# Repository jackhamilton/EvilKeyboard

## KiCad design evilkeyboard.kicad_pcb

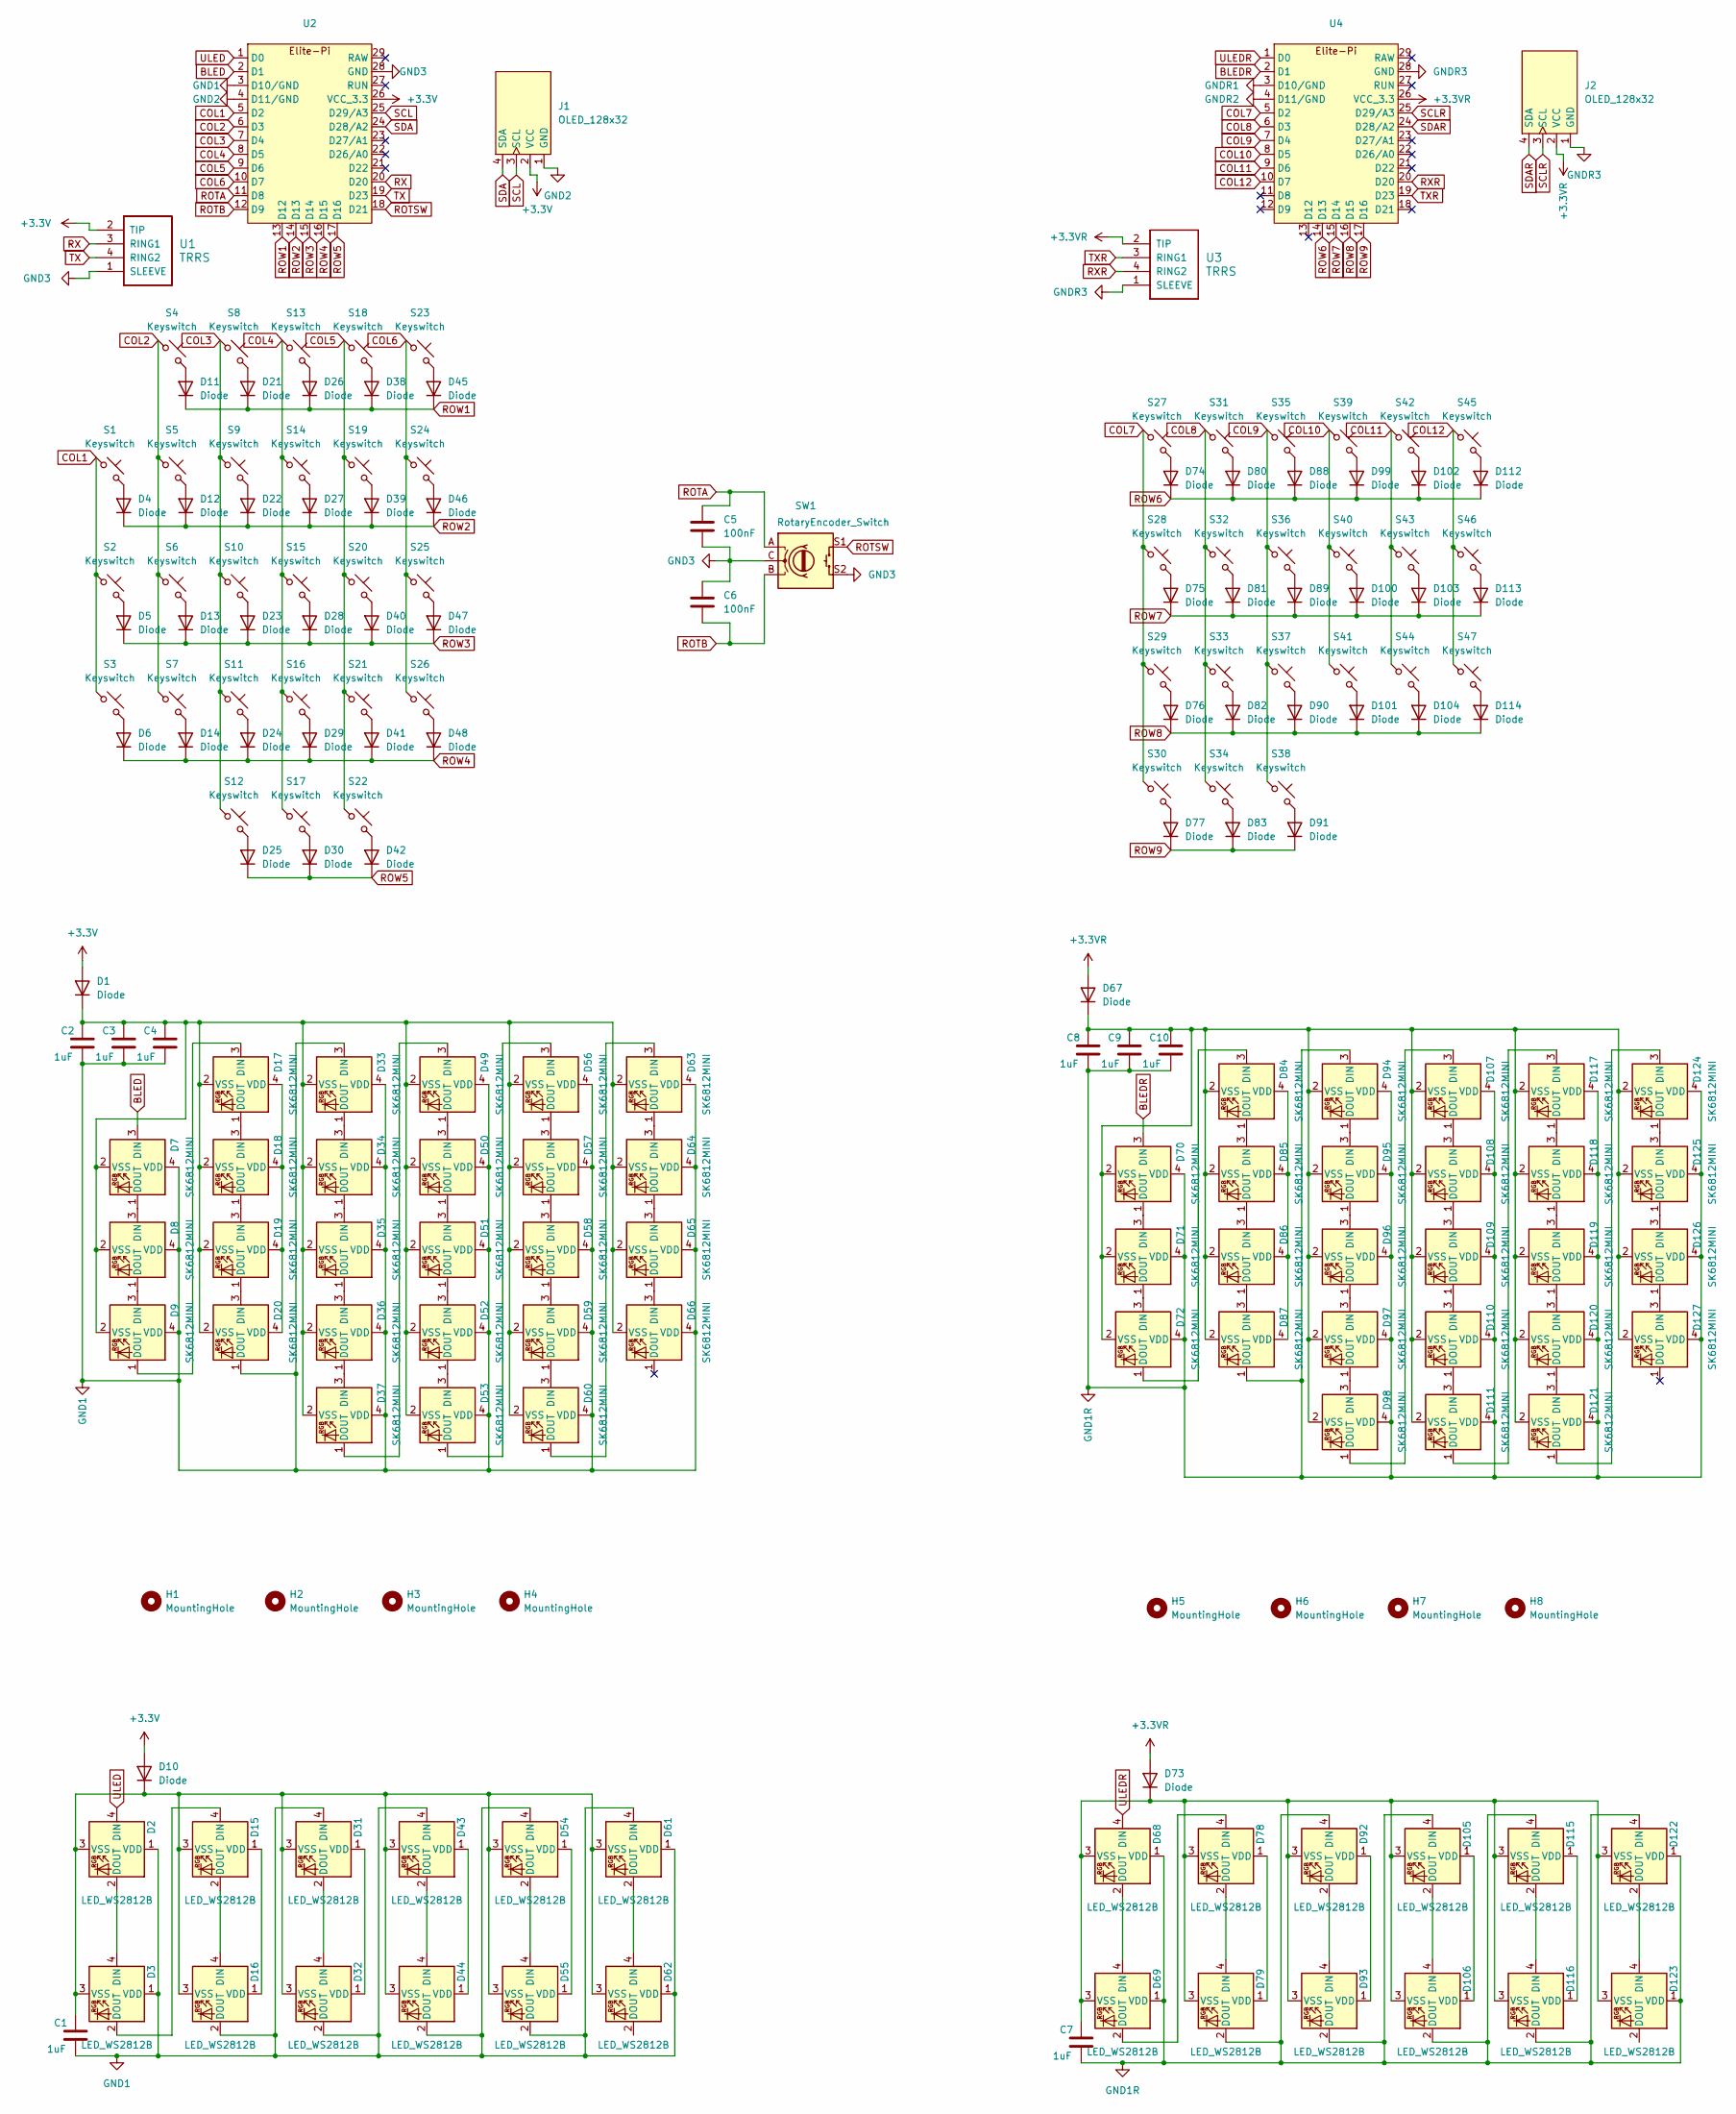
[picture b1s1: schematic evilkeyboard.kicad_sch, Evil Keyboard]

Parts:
C1, C2, C3, C4, C7, C8, C9, C10: 1uF; C_0201_0603Metric_Pad0.64x0.40mm_HandSolder
C5, C6: 100nF; C_0201_0603Metric_Pad0.64x0.40mm_HandSolder
D1, D4, D5, D6, D10, D11, D12, D13, D14, D21, D22, D23, D24, D25, D26, D27, D28, D29, D30, D38, D39, D40, D41, D42, D45, D46, D47, D48, D67, D73, D74, D75, D76, D77, D80, D81, D82, D83, D88, D89, D90, D91, D99, D100, D101, D102, D103, D104, D112, D113, D114: Diode
D2, D3, D15, D16, D31, D32, D43, D44, D54, D55, D61, D62, D68, D69, D78, D79, D92, D93, D105, D106, D115, D116, D122, D123: LED_WS2812B
D7, D8, D9, D17, D18, D19, D20, D33, D34, D35, D36, D37, D49, D50, D51, D52, D53, D56, D57, D58, D59, D60, D63, D64, D65, D66, D70, D71, D72, D84, D85, D86, D87, D94, D95, D96, D97, D98, D107, D108, D109, D110, D111, D117, D118, D119, D120, D121, D124, D125, D126, D127: SK6812MINI; LED_SK6812MINI_PLCC4_3.5x3.5mm_P1.75mm
H1, H2, H3, H4, H5, H6, H7, H8: MountingHole; MountingHole_2.7mm
J1, J2: OLED_128x32
S1, S2, S3, S4, S5, S6, S7, S8, S9, S10, S11, S12, S13, S14, S15, S16, S17, S18, S19, S20, S21, S22, S23, S24, S25, S26, S27, S28, S29, S30, S31, S32, S33, S34, S35, S36, S37, S38, S39, S40, S41, S42, S43, S44, S45, S46, S47: Keyswitch; Kailh_socket_PG1350
SW1: RotaryEncoder_Switch; RotaryEncoder_EC11
U1, U3: TRRS; TRRS_PJ-320A
U2, U4: Elite-C

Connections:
TX: U1.4 (RING2), U2.19 (D23)
TXR: U3.3 (RING1), U4.19 (D23)
+3.3V: D1.2 (A), D10.2 (A), J1.2 (VCC), U1.2 (TIP), U2.26 (VCC_3.3)
+3.3VR: D67.2 (A), D73.2 (A), J2.2 (VCC), U3.2 (TIP), U4.26 (VCC_3.3)
BLED: D7.3 (DIN), U2.2 (D1)
BLEDR: D70.3 (DIN), U4.2 (D1)
COL1: S1.1, S2.1, S3.1, U2.5 (D2)
COL2: S4.1, S5.1, S6.1, S7.1, U2.6 (D3)
COL3: S8.1, S9.1, S10.1, S11.1, S12.1, U2.7 (D4)
COL4: S13.1, S14.1, S15.1, S16.1, S17.1, U2.8 (D5)
COL5: S18.1, S19.1, S20.1, S21.1, S22.1, U2.9 (D6)
COL6: S23.1, S24.1, S25.1, S26.1, U2.10 (D7)
COL7: S27.1, S28.1, S29.1, S30.1, U4.5 (D2)
COL8: S31.1, S32.1, S33.1, S34.1, U4.6 (D3)
COL9: S35.1, S36.1, S37.1, S38.1, U4.7 (D4)
COL10: S39.1, S40.1, S41.1, U4.8 (D5)
COL11: S42.1, S43.1, S44.1, U4.9 (D6)
COL12: S45.1, S46.1, S47.1, U4.10 (D7)
GND1: C1.2, C2.2, C3.2, C4.2, D2.1 (VDD), D3.1 (VDD), D7.4 (VDD), D8.4 (VDD), D9.4 (VDD), D16.2 (DOUT), D20.1 (DOUT), D31.4 (DIN), D32.2 (DOUT), D33.3 (DIN), D33.4 (VDD), D34.4 (VDD), D35.4 (VDD), D36.4 (VDD), D37.4 (VDD), D43.4 (DIN), D44.2 (DOUT), D49.4 (VDD), D50.4 (VDD), D51.4 (VDD), D52.4 (VDD), D53.4 (VDD), D54.4 (DIN), D55.2 (DOUT), D56.4 (VDD), D57.4 (VDD), D58.4 (VDD), D59.4 (VDD), D60.4 (VDD), D61.1 (VDD), D61.4 (DIN), D62.1 (VDD), D63.4 (VDD), D64.4 (VDD), D65.4 (VDD), D66.4 (VDD), U2.3 (D10/GND)
GND1R: C7.2, C8.2, C9.2, C10.2, D68.1 (VDD), D69.1 (VDD), D70.4 (VDD), D71.4 (VDD), D72.4 (VDD), D79.2 (DOUT), D87.1 (DOUT), D92.4 (DIN), D93.2 (DOUT), D94.3 (DIN), D94.4 (VDD), D95.4 (VDD), D96.4 (VDD), D97.4 (VDD), D98.4 (VDD), D105.4 (DIN), D106.2 (DOUT), D107.4 (VDD), D108.4 (VDD), D109.4 (VDD), D110.4 (VDD), D111.4 (VDD), D115.4 (DIN), D116.2 (DOUT), D117.4 (VDD), D118.4 (VDD), D119.4 (VDD), D120.4 (VDD), D121.4 (VDD), D122.1 (VDD), D122.4 (DIN), D123.1 (VDD), D124.4 (VDD), D125.4 (VDD), D126.4 (VDD), D127.4 (VDD)
GND2: J1.1 (GND), U2.4 (D11/GND)
GND3: C5.2, C6.1, SW1.C, SW1.S2, U1.1 (SLEEVE), U2.28 (GND)
GNDR1: U4.3 (D10/GND)
GNDR2: U4.4 (D11/GND)
GNDR3: J2.1 (GND), U3.1 (SLEEVE), U4.28 (GND)
unnamed: C2.1, C3.1, C4.1, D1.1 (K), D7.2 (VSS), D8.2 (VSS), D9.2 (VSS), D17.2 (VSS), D18.2 (VSS), D19.2 (VSS), D20.2 (VSS), D33.2 (VSS), D34.2 (VSS), D35.2 (VSS), D36.2 (VSS), D37.2 (VSS), D49.2 (VSS), D50.2 (VSS), D51.2 (VSS), D52.2 (VSS), D53.2 (VSS), D56.2 (VSS), D57.2 (VSS), D58.2 (VSS), D59.2 (VSS), D60.2 (VSS), D63.2 (VSS), D64.2 (VSS), D65.2 (VSS), D66.2 (VSS)
unnamed: D2.2 (DOUT), D3.4 (DIN)
unnamed: D4.2 (A), S1.2
unnamed: D5.2 (A), S2.2
unnamed: D6.2 (A), S3.2
unnamed: D7.1 (DOUT), D8.3 (DIN)
unnamed: D8.1 (DOUT), D9.3 (DIN)
unnamed: C1.1, D2.3 (VSS), D3.3 (VSS), D10.1 (K), D15.3 (VSS), D16.3 (VSS), D31.3 (VSS), D32.3 (VSS), D43.3 (VSS), D44.3 (VSS), D54.3 (VSS), D55.3 (VSS), D61.3 (VSS), D62.3 (VSS)
unnamed: D11.2 (A), S4.2
unnamed: D12.2 (A), S5.2
unnamed: D13.2 (A), S6.2
unnamed: D14.2 (A), S7.2
unnamed: D3.2 (DOUT), D15.4 (DIN)
unnamed: D15.2 (DOUT), D16.4 (DIN)
unnamed: D15.1 (VDD), D16.1 (VDD)
unnamed: D9.1 (DOUT), D17.3 (DIN)
unnamed: D17.1 (DOUT), D18.3 (DIN)
unnamed: D17.4 (VDD), D18.4 (VDD), D19.4 (VDD), D20.4 (VDD)
unnamed: D18.1 (DOUT), D19.3 (DIN)
unnamed: D19.1 (DOUT), D20.3 (DIN)
unnamed: D21.2 (A), S8.2
unnamed: D22.2 (A), S9.2
unnamed: D23.2 (A), S10.2
unnamed: D24.2 (A), S11.2
unnamed: D25.2 (A), S12.2
unnamed: D26.2 (A), S13.2
unnamed: D27.2 (A), S14.2
unnamed: D28.2 (A), S15.2
unnamed: D29.2 (A), S16.2
unnamed: D30.2 (A), S17.2
unnamed: D31.2 (DOUT), D32.4 (DIN)
unnamed: D31.1 (VDD), D32.1 (VDD)
unnamed: D33.1 (DOUT), D34.3 (DIN)
unnamed: D34.1 (DOUT), D35.3 (DIN)
unnamed: D35.1 (DOUT), D36.3 (DIN)
unnamed: D36.1 (DOUT), D37.3 (DIN)
unnamed: D37.1 (DOUT), D49.3 (DIN)
unnamed: D38.2 (A), S18.2
unnamed: D39.2 (A), S19.2
unnamed: D40.2 (A), S20.2
unnamed: D41.2 (A), S21.2
unnamed: D42.2 (A), S22.2
unnamed: D43.2 (DOUT), D44.4 (DIN)
unnamed: D43.1 (VDD), D44.1 (VDD)
unnamed: D45.2 (A), S23.2
unnamed: D46.2 (A), S24.2
unnamed: D47.2 (A), S25.2
unnamed: D48.2 (A), S26.2
unnamed: D49.1 (DOUT), D50.3 (DIN)
unnamed: D50.1 (DOUT), D51.3 (DIN)
unnamed: D51.1 (DOUT), D52.3 (DIN)
unnamed: D52.1 (DOUT), D53.3 (DIN)
unnamed: D53.1 (DOUT), D56.3 (DIN)
unnamed: D54.2 (DOUT), D55.4 (DIN)
unnamed: D54.1 (VDD), D55.1 (VDD)
unnamed: D56.1 (DOUT), D57.3 (DIN)
unnamed: D57.1 (DOUT), D58.3 (DIN)
unnamed: D58.1 (DOUT), D59.3 (DIN)
unnamed: D59.1 (DOUT), D60.3 (DIN)
unnamed: D60.1 (DOUT), D63.3 (DIN)
unnamed: D61.2 (DOUT), D62.4 (DIN)
unnamed: D63.1 (DOUT), D64.3 (DIN)
unnamed: D64.1 (DOUT), D65.3 (DIN)
unnamed: D65.1 (DOUT), D66.3 (DIN)
unnamed: D68.2 (DOUT), D69.4 (DIN)
unnamed: D69.2 (DOUT), D78.4 (DIN)
unnamed: D70.1 (DOUT), D71.3 (DIN)
unnamed: D71.1 (DOUT), D72.3 (DIN)
unnamed: D72.1 (DOUT), D84.3 (DIN)
unnamed: D74.2 (A), S27.2
unnamed: D75.2 (A), S28.2
unnamed: D76.2 (A), S29.2
unnamed: D77.2 (A), S30.2
unnamed: D78.2 (DOUT), D79.4 (DIN)
unnamed: D78.1 (VDD), D79.1 (VDD)
unnamed: D80.2 (A), S31.2
unnamed: D81.2 (A), S32.2
unnamed: D82.2 (A), S33.2
unnamed: D83.2 (A), S34.2
unnamed: D84.1 (DOUT), D85.3 (DIN)
unnamed: D84.4 (VDD), D85.4 (VDD), D86.4 (VDD), D87.4 (VDD)
unnamed: D85.1 (DOUT), D86.3 (DIN)
unnamed: D86.1 (DOUT), D87.3 (DIN)
unnamed: D88.2 (A), S35.2
unnamed: D89.2 (A), S36.2
unnamed: D90.2 (A), S37.2
unnamed: D91.2 (A), S38.2
unnamed: D92.2 (DOUT), D93.4 (DIN)
unnamed: D92.1 (VDD), D93.1 (VDD)
unnamed: D94.1 (DOUT), D95.3 (DIN)
unnamed: D95.1 (DOUT), D96.3 (DIN)
unnamed: D96.1 (DOUT), D97.3 (DIN)
unnamed: D97.1 (DOUT), D98.3 (DIN)
unnamed: D99.2 (A), S39.2
unnamed: D100.2 (A), S40.2
unnamed: D101.2 (A), S41.2
unnamed: D102.2 (A), S42.2
unnamed: D103.2 (A), S43.2
unnamed: D104.2 (A), S44.2
unnamed: D105.2 (DOUT), D106.4 (DIN)
unnamed: D105.1 (VDD), D106.1 (VDD)
unnamed: C7.1, D68.3 (VSS), D69.3 (VSS), D73.1 (K), D78.3 (VSS), D79.3 (VSS), D92.3 (VSS), D93.3 (VSS), D105.3 (VSS), D106.3 (VSS), D115.3 (VSS), D116.3 (VSS), D122.3 (VSS), D123.3 (VSS)
unnamed: D98.1 (DOUT), D107.3 (DIN)
unnamed: D107.1 (DOUT), D108.3 (DIN)
unnamed: C8.1, C9.1, C10.1, D67.1 (K), D70.2 (VSS), D71.2 (VSS), D72.2 (VSS), D84.2 (VSS), D85.2 (VSS), D86.2 (VSS), D87.2 (VSS), D94.2 (VSS), D95.2 (VSS), D96.2 (VSS), D97.2 (VSS), D98.2 (VSS), D107.2 (VSS), D108.2 (VSS), D109.2 (VSS), D110.2 (VSS), D111.2 (VSS), D117.2 (VSS), D118.2 (VSS), D119.2 (VSS), D120.2 (VSS), D121.2 (VSS), D124.2 (VSS), D125.2 (VSS), D126.2 (VSS), D127.2 (VSS)
unnamed: D108.1 (DOUT), D109.3 (DIN)
unnamed: D109.1 (DOUT), D110.3 (DIN)
unnamed: D110.1 (DOUT), D111.3 (DIN)
unnamed: D111.1 (DOUT), D117.3 (DIN)
unnamed: D112.2 (A), S45.2
unnamed: D113.2 (A), S46.2
unnamed: D114.2 (A), S47.2
unnamed: D115.2 (DOUT), D116.4 (DIN)
unnamed: D115.1 (VDD), D116.1 (VDD)
unnamed: D117.1 (DOUT), D118.3 (DIN)
unnamed: D118.1 (DOUT), D119.3 (DIN)
unnamed: D119.1 (DOUT), D120.3 (DIN)
unnamed: D120.1 (DOUT), D121.3 (DIN)
unnamed: D121.1 (DOUT), D124.3 (DIN)
unnamed: D122.2 (DOUT), D123.4 (DIN)
unnamed: D124.1 (DOUT), D125.3 (DIN)
unnamed: D125.1 (DOUT), D126.3 (DIN)
unnamed: D126.1 (DOUT), D127.3 (DIN)
ROTA: C5.1, SW1.A, U2.11 (D8)
ROTB: C6.2, SW1.B, U2.12 (D9)
ROTSW: SW1.S1, U2.18 (D21)
ROW1: D11.1 (K), D21.1 (K), D26.1 (K), D38.1 (K), D45.1 (K), U2.13 (D12)
ROW2: D4.1 (K), D12.1 (K), D22.1 (K), D27.1 (K), D39.1 (K), D46.1 (K), U2.14 (D13)
ROW3: D5.1 (K), D13.1 (K), D23.1 (K), D28.1 (K), D40.1 (K), D47.1 (K), U2.15 (D14)
ROW4: D6.1 (K), D14.1 (K), D24.1 (K), D29.1 (K), D41.1 (K), D48.1 (K), U2.16 (D15)
ROW5: D25.1 (K), D30.1 (K), D42.1 (K), U2.17 (D16)
ROW6: D74.1 (K), D80.1 (K), D88.1 (K), D99.1 (K), D102.1 (K), D112.1 (K), U4.14 (D13)
ROW7: D75.1 (K), D81.1 (K), D89.1 (K), D100.1 (K), D103.1 (K), D113.1 (K), U4.15 (D14)
ROW8: D76.1 (K), D82.1 (K), D90.1 (K), D101.1 (K), D104.1 (K), D114.1 (K), U4.16 (D15)
ROW9: D77.1 (K), D83.1 (K), D91.1 (K), U4.17 (D16)
RX: U1.3 (RING1), U2.20 (D20)
RXR: U3.4 (RING2), U4.20 (D20)
SCL: J1.3 (SCL), U2.25 (D29/A3)
SCLR: J2.3 (SCL), U4.25 (D29/A3)
SDA: J1.4 (SDA), U2.24 (D28/A2)
SDAR: J2.4 (SDA), U4.24 (D28/A2)
ULED: D2.4 (DIN), U2.1 (D0)
ULEDR: D68.4 (DIN), U4.1 (D0)

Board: 2 copper layers, 199 parts (50 on the bottom side), 166 nets, no tracks yet.

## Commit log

2024-04-18 Evil keyboard schematic
2024-04-20 Revision 1
2024-04-21 basic pcb layout
